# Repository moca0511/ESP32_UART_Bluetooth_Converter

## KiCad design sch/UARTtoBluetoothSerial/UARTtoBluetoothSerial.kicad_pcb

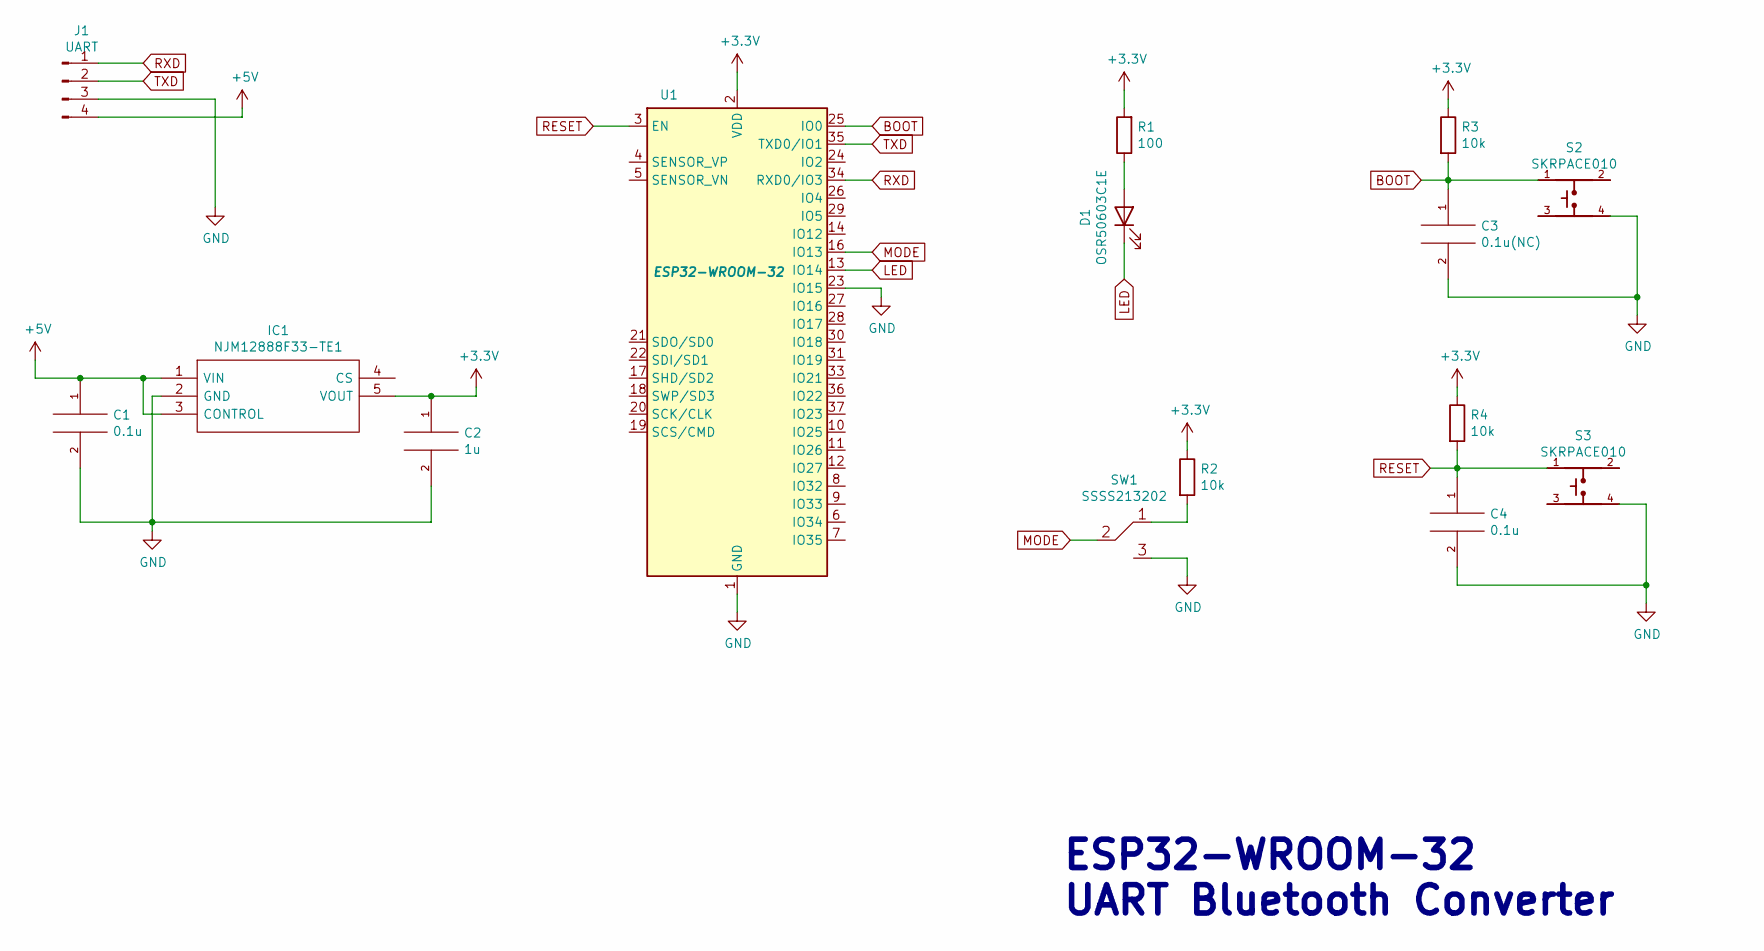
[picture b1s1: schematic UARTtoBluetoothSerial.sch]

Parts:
C1, C4: 0.1u; C_0603_1608Metric
C2: 1u; C_0603_1608Metric
C3: 0.1u(NC); C_0603_1608Metric
D1: OSR50603C1E; LED_0603_1608Metric
IC1: NJM12888F33-TE1; SOT95P280X130-5N; Manufacturer_Part_Number NJM12888F33-TE1; Mouser Part Number 513-NJM12888F33-TE1
J1: UART; PinSocket_1x04_P2.54mm_Vertical
R1: 100; R_0603_1608Metric
R2, R3, R4: 10k; R_0603_1608Metric
S2, S3: SKRPACE010; SW_SKRPACE010
SW1: SSSS213202
U1: ESP32-WROOM-32

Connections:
+3V3: C2.1, IC1.5 (VOUT), R1.2, R2.1, R3.1, R4.1, U1.2 (VDD)
+5V: C1.1, IC1.1 (VIN), IC1.3 (CONTROL), J1.4
BOOT: C3.1, R3.2, S2.1, U1.25 (IO0)
GND: C1.2, C2.2, C3.2, C4.2, IC1.2 (GND), J1.3, S2.4, S3.4, SW1.3, U1.1 (GND), U1.15 (GND), U1.23 (IO15), U1.38 (GND), U1.39 (GND)
LED: D1.1 (K), U1.13 (IO14)
MODE: SW1.2, U1.16 (IO13)
unnamed: D1.2 (A), R1.1
unnamed: R2.2, SW1.1
RESET: C4.1, R4.2, S3.1, U1.3 (EN)
RXD: J1.1, U1.34 (RXD0/IO3)
TXD: J1.2, U1.35 (TXD0/IO1)

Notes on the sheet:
ESP32-WROOM-32 UART Bluetooth Converter

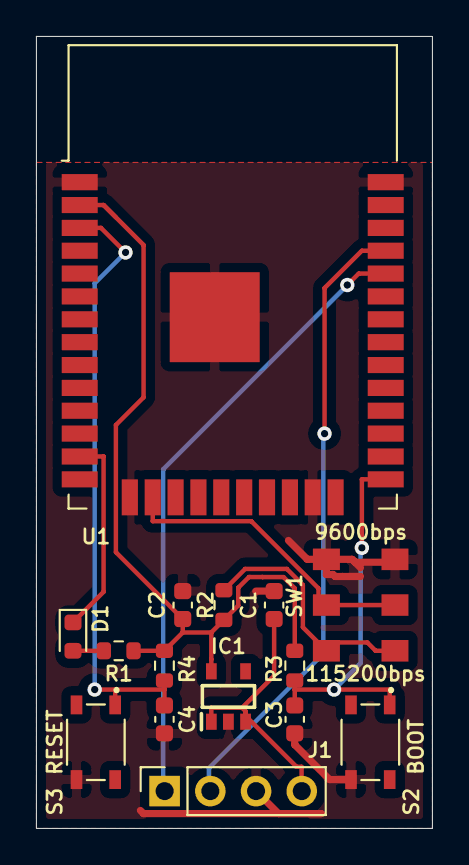
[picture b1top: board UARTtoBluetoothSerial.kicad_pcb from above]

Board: 2 copper layers, 22.0 x 44.0 mm, 15 parts (0 on the bottom side), 11 nets.

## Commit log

2020-10-28 kicadライブラリのpath調整
2020-10-28 ディレクトリ構成変更
2020-12-22 回路図修正
2020-12-22 LED抵抗値修正
2021-01-11 readme 追記
2021-01-11 no message
